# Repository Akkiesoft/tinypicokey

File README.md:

# TinyPicoKey

[Pimoroni Tiny 2040](https://shop.pimoroni.com/products/tiny-2040)に組み合わせて使用できる1キーだけのキーボード用基板です。Tiny 2040のGP6に接続されています。

## 制作環境

KiCad (6.0)

## ボード

### TinyPicoKey

Cherry MXおよび互換キースイッチ用ボードです

### TinyPicoKey-LP

Kailhロープロファイルスイッチ（PG1350）用ボードです

### TinyPicoTrio

TinyPicoKeyを3つ搭載できるボードです。TinyPicoKeyは上下逆に取り付けても動作します。左からGP4、GP5、GP6に接続されていて、右のキーはTinyPicoKey単体で使用する場合と共用です。

## 組み立て例

ピンヘッダ/ピンソケットは以下のパーツがおすすめです。

* [ロープロファイルピンヘッダ 7.7mm（低オス） 1x40（40P）](https://akizukidenshi.com/catalog/g/gC-02900/)
* [シングルピンソケット （低メス） 1x20 （20P）](https://akizukidenshi.com/catalog/g/gC-03138/)

TinyPicoKeyにピンヘッダを、Tiny 2040にピンソケットをはんだ付けすることをおすすめします。

## サンプルスクリプト

CircuitPythonで使うサンプルです。

## License

board-tinypicokey-lp/Library.pretty/SW_PG1350.kicad_mod from [daprice/keyswitches.pretty](https://github.com/daprice/keyswitches.pretty) is licensed under a [Creative Commons Attribution-ShareAlike 4.0 International License](https://creativecommons.org/licenses/by-sa/4.0/). We added a modification to remove the border line.

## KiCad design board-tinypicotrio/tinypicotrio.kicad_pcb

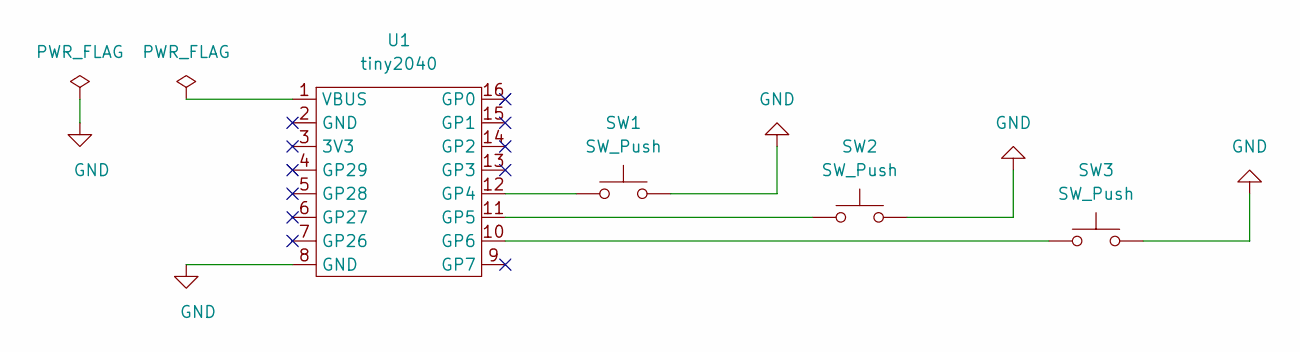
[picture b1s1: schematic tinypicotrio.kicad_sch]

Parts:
SW1, SW2, SW3: SW_Push; tinypicokey
U1: tiny2040; tiny2040_wo_debug

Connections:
GND: SW1.2, SW2.2, SW3.2, U1.8 (GND)
unnamed: SW1.1, U1.12 (GP4)
unnamed: SW2.1, U1.11 (GP5)
unnamed: SW3.1, U1.10 (GP6)

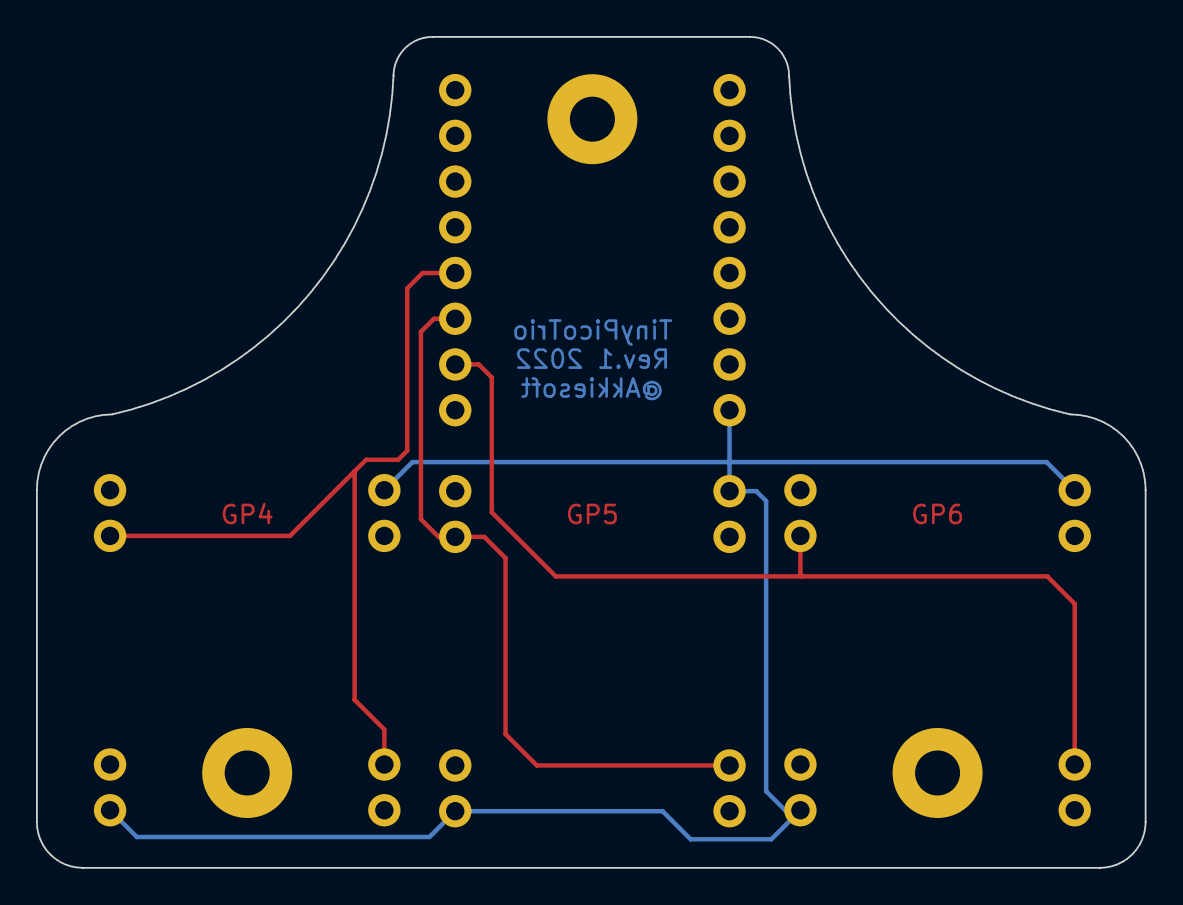
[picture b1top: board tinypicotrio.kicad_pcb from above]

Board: 2 copper layers, 61.6 x 46.2 mm, 4 parts (1 on the bottom side), 4 nets.

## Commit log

2021-10-20 init
2021-11-13 Rev.2
    * resize through holes from 0.7mm to 1.02mm
    * add strap hole
2022-06-18 Rev.3
    * expanded the strap hole
    * change board image
2022-06-18 rename directory
2022-06-18 Add TinyPicoKey-LP Rev.1
2022-06-18 Add TinyPicoTrio Rev.1
2023-08-14 add sample for picotrio
2023-11-29 update sample-picotrio-abc.py
    * replace some arrays with tuple
    * support to sending string
    * change the logic in main loop
